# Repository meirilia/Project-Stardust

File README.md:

# Project Stardust

A custom keyboard created to mimick the layout of thinkpad's keyboard + some layout improvement (i guess).

**The layout :**

PCB for trackpoint module will come soon (hopefully...) + The application for directly configuring the keyboard

I will not procrastinate 
I will not procrastinate 
I will not procrastinate 
I will not procrastinate 
I will not procrastinate 
I will not procrastinate

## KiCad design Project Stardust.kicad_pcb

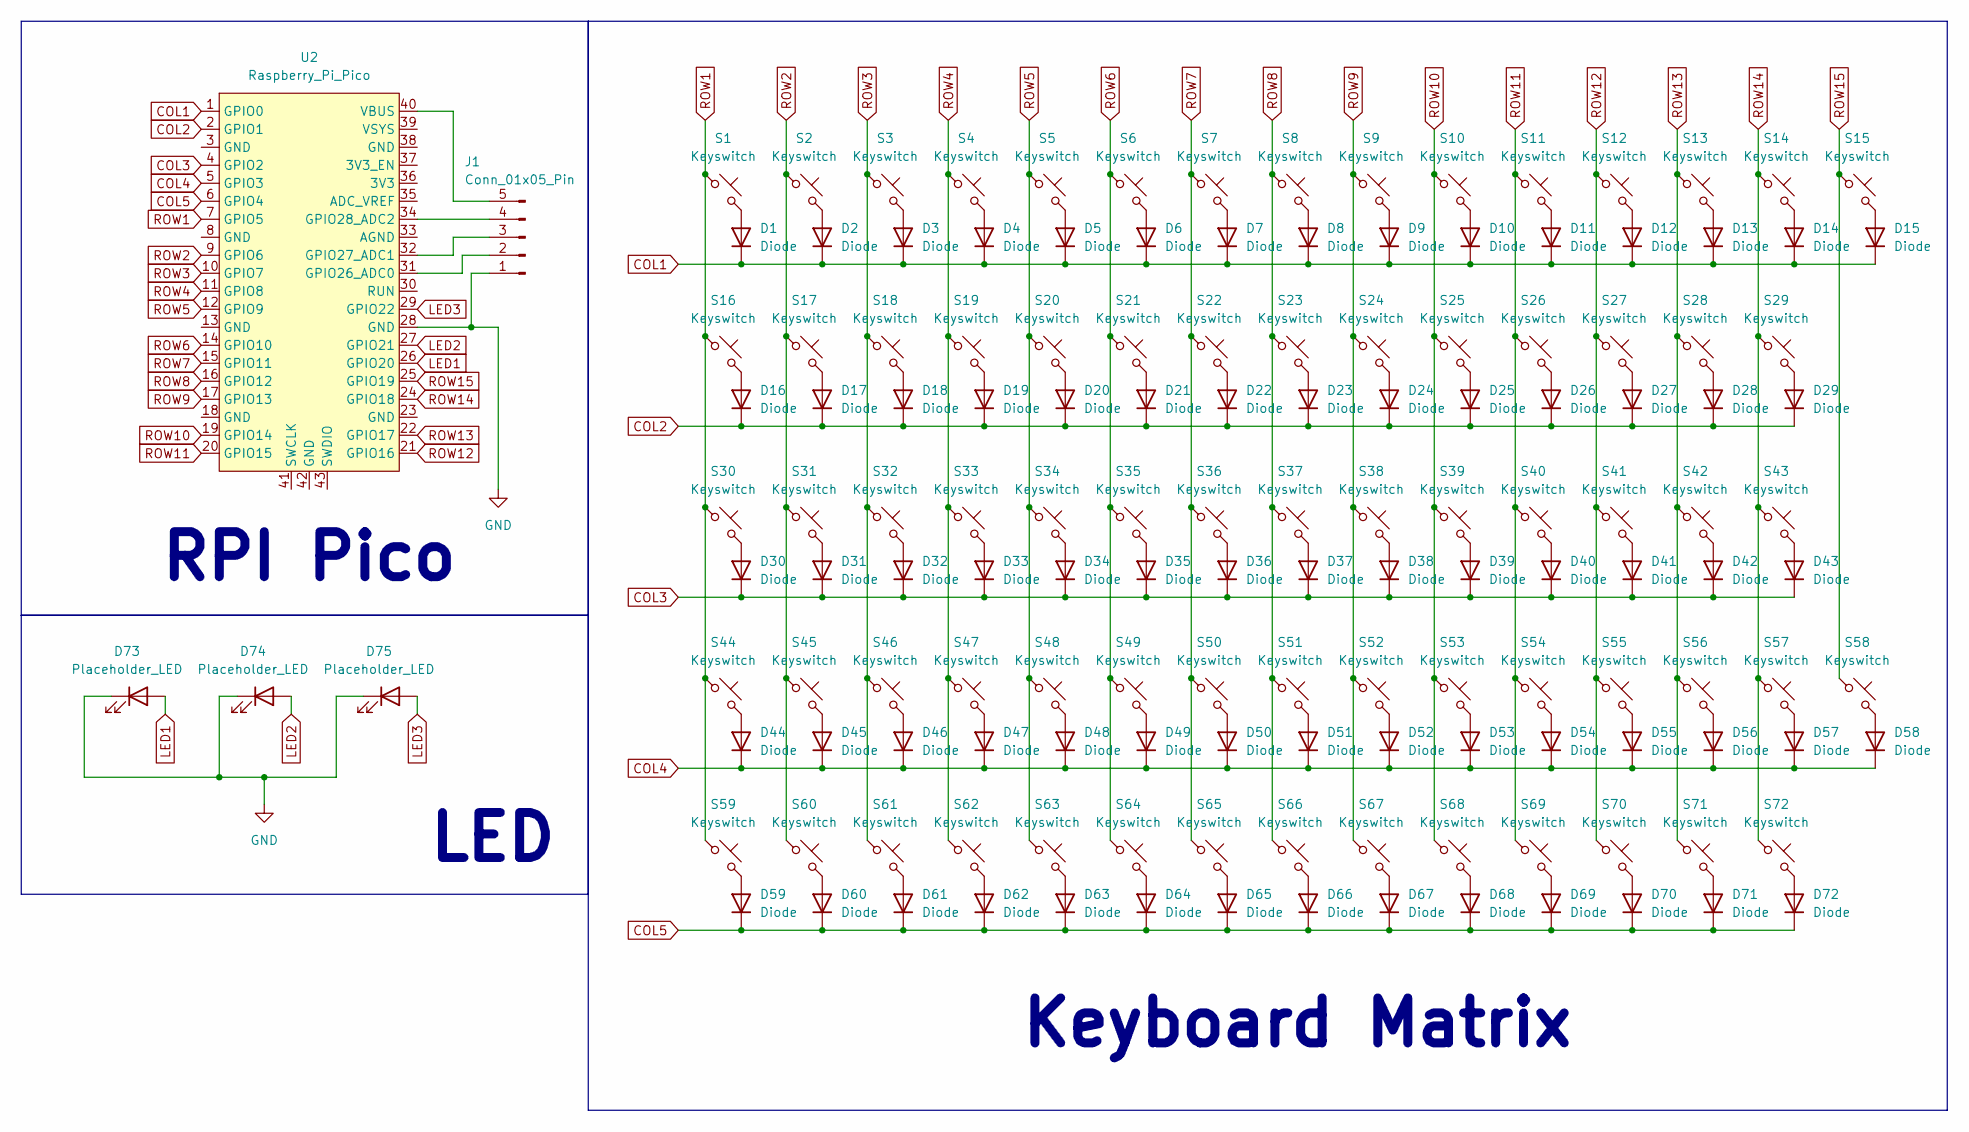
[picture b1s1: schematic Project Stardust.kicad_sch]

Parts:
D1, D2, D3, D4, D5, D6, D7, D8, D9, D10, D11, D12, D13, D14, D15, D16, D17, D18, D19, D20, D21, D22, D23, D24, D25, D26, D27, D28, D29, D30, D31, D32, D33, D34, D35, D36, D37, D38, D39, D40, D41, D42, D43, D44, D45, D46, D47, D48, D49, D50, D51, D52, D53, D54, D55, D56, D57, D58, D59, D60, D61, D62, D63, D64, D65, D66, D67, D68, D69, D70, D71, D72: Diode; Diode_DO-35
D73, D74, D75: Placeholder_LED; LED_D5.0mm
J1: Conn_01x05_Pin; SolderWire-0.5sqmm_1x05_P4.8mm_D0.9mm_OD2.3mm_Relief
S1, S2, S3, S4, S5, S6, S7, S8, S9, S10, S11, S12, S13, S14, S15, S17, S18, S19, S20, S21, S22, S23, S24, S25, S26, S27, S28, S31, S32, S33, S34, S35, S36, S37, S38, S39, S40, S41, S43, S45, S46, S47, S48, S49, S50, S51, S52, S53, S55, S56, S57, S58, S59, S61, S62, S64, S65, S66, S69, S70, S71, S72: Keyswitch; Hotswap_MX_1.00u
S16, S29: Keyswitch; Hotswap_MX_1.50u
S30, S54: Keyswitch; Hotswap_MX_1.75u
S42, S44, S63: Keyswitch; Hotswap_MX_2.25u
S60, S68: Keyswitch; Hotswap_MX_1.25u
S67: Keyswitch; Hotswap_MX_2.75u
U2: Raspberry_Pi_Pico

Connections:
COL1: D1.1 (K), D2.1 (K), D3.1 (K), D4.1 (K), D5.1 (K), D6.1 (K), D7.1 (K), D8.1 (K), D9.1 (K), D10.1 (K), D11.1 (K), D12.1 (K), D13.1 (K), D14.1 (K), D15.1 (K), U2.1 (GPIO0)
COL2: D16.1 (K), D17.1 (K), D18.1 (K), D19.1 (K), D20.1 (K), D21.1 (K), D22.1 (K), D23.1 (K), D24.1 (K), D25.1 (K), D26.1 (K), D27.1 (K), D28.1 (K), D29.1 (K), U2.2 (GPIO1)
COL3: D30.1 (K), D31.1 (K), D32.1 (K), D33.1 (K), D34.1 (K), D35.1 (K), D36.1 (K), D37.1 (K), D38.1 (K), D39.1 (K), D40.1 (K), D41.1 (K), D42.1 (K), D43.1 (K), U2.4 (GPIO2)
COL4: D44.1 (K), D45.1 (K), D46.1 (K), D47.1 (K), D48.1 (K), D49.1 (K), D50.1 (K), D51.1 (K), D52.1 (K), D53.1 (K), D54.1 (K), D55.1 (K), D56.1 (K), D57.1 (K), D58.1 (K), U2.5 (GPIO3)
COL5: D59.1 (K), D60.1 (K), D61.1 (K), D62.1 (K), D63.1 (K), D64.1 (K), D65.1 (K), D66.1 (K), D67.1 (K), D68.1 (K), D69.1 (K), D70.1 (K), D71.1 (K), D72.1 (K), U2.6 (GPIO4)
GND: D73.1 (K), D74.1 (K), D75.1 (K), J1.1, U2.28 (GND)
LED1: D73.2 (A), U2.26 (GPIO20)
LED2: D74.2 (A), U2.27 (GPIO21)
LED3: D75.2 (A), U2.29 (GPIO22)
unnamed: D1.2 (A), S1.2
unnamed: D2.2 (A), S2.2
unnamed: D3.2 (A), S3.2
unnamed: D4.2 (A), S4.2
unnamed: D5.2 (A), S5.2
unnamed: D6.2 (A), S6.2
unnamed: D7.2 (A), S7.2
unnamed: D8.2 (A), S8.2
unnamed: D9.2 (A), S9.2
unnamed: D10.2 (A), S10.2
unnamed: D11.2 (A), S11.2
unnamed: D12.2 (A), S12.2
unnamed: D13.2 (A), S13.2
unnamed: D14.2 (A), S14.2
unnamed: D15.2 (A), S15.2
unnamed: D16.2 (A), S16.2
unnamed: D17.2 (A), S17.2
unnamed: D18.2 (A), S18.2
unnamed: D19.2 (A), S19.2
unnamed: D20.2 (A), S20.2
unnamed: D21.2 (A), S21.2
unnamed: D22.2 (A), S22.2
unnamed: D23.2 (A), S23.2
unnamed: D24.2 (A), S24.2
unnamed: D25.2 (A), S25.2
unnamed: D26.2 (A), S26.2
unnamed: D27.2 (A), S27.2
unnamed: D28.2 (A), S28.2
unnamed: D29.2 (A), S29.2
unnamed: D30.2 (A), S30.2
unnamed: D31.2 (A), S31.2
unnamed: D32.2 (A), S32.2
unnamed: D33.2 (A), S33.2
unnamed: D34.2 (A), S34.2
unnamed: D35.2 (A), S35.2
unnamed: D36.2 (A), S36.2
unnamed: D37.2 (A), S37.2
unnamed: D38.2 (A), S38.2
unnamed: D39.2 (A), S39.2
unnamed: D40.2 (A), S40.2
unnamed: D41.2 (A), S41.2
unnamed: D42.2 (A), S42.2
unnamed: D43.2 (A), S43.2
unnamed: D44.2 (A), S44.2
unnamed: D45.2 (A), S45.2
unnamed: D46.2 (A), S46.2
unnamed: D47.2 (A), S47.2
unnamed: D48.2 (A), S48.2
unnamed: D49.2 (A), S49.2
unnamed: D50.2 (A), S50.2
unnamed: D51.2 (A), S51.2
unnamed: D52.2 (A), S52.2
unnamed: D53.2 (A), S53.2
unnamed: D54.2 (A), S54.2
unnamed: D55.2 (A), S55.2
unnamed: D56.2 (A), S56.2
unnamed: D57.2 (A), S57.2
unnamed: D58.2 (A), S58.2
unnamed: D59.2 (A), S59.2
unnamed: D60.2 (A), S60.2
unnamed: D61.2 (A), S61.2
unnamed: D62.2 (A), S62.2
unnamed: D63.2 (A), S63.2
unnamed: D64.2 (A), S64.2
unnamed: D65.2 (A), S65.2
unnamed: D66.2 (A), S66.2
unnamed: D67.2 (A), S67.2
unnamed: D68.2 (A), S68.2
unnamed: D69.2 (A), S69.2
unnamed: D70.2 (A), S70.2
unnamed: D71.2 (A), S71.2
unnamed: D72.2 (A), S72.2
unnamed: J1.2, U2.31 (GPIO26_ADC0)
unnamed: J1.3, U2.32 (GPIO27_ADC1)
unnamed: J1.4, U2.34 (GPIO28_ADC2)
unnamed: J1.5, U2.40 (VBUS)
ROW1: S1.1, S16.1, S30.1, S44.1, S59.1, U2.7 (GPIO5)
ROW2: S2.1, S17.1, S31.1, S45.1, S60.1, U2.9 (GPIO6)
ROW3: S3.1, S18.1, S32.1, S46.1, S61.1, U2.10 (GPIO7)
ROW4: S4.1, S19.1, S33.1, S47.1, S62.1, U2.11 (GPIO8)
ROW5: S5.1, S20.1, S34.1, S48.1, S63.1, U2.12 (GPIO9)
ROW6: S6.1, S21.1, S35.1, S49.1, S64.1, U2.14 (GPIO10)
ROW7: S7.1, S22.1, S36.1, S50.1, S65.1, U2.15 (GPIO11)
ROW8: S8.1, S23.1, S37.1, S51.1, S66.1, U2.16 (GPIO12)
ROW9: S9.1, S24.1, S38.1, S52.1, S67.1, U2.17 (GPIO13)
ROW10: S10.1, S25.1, S39.1, S53.1, S68.1, U2.19 (GPIO14)
ROW11: S11.1, S26.1, S40.1, S54.1, S69.1, U2.20 (GPIO15)
ROW12: S12.1, S27.1, S41.1, S55.1, S70.1, U2.21 (GPIO16)
ROW13: S13.1, S28.1, S42.1, S56.1, S71.1, U2.22 (GPIO17)
ROW14: S14.1, S29.1, S43.1, S57.1, S72.1, U2.24 (GPIO18)
ROW15: S15.1, S58.1, U2.25 (GPIO19)

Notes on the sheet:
LED
RPI Pico
Keyboard Matrix

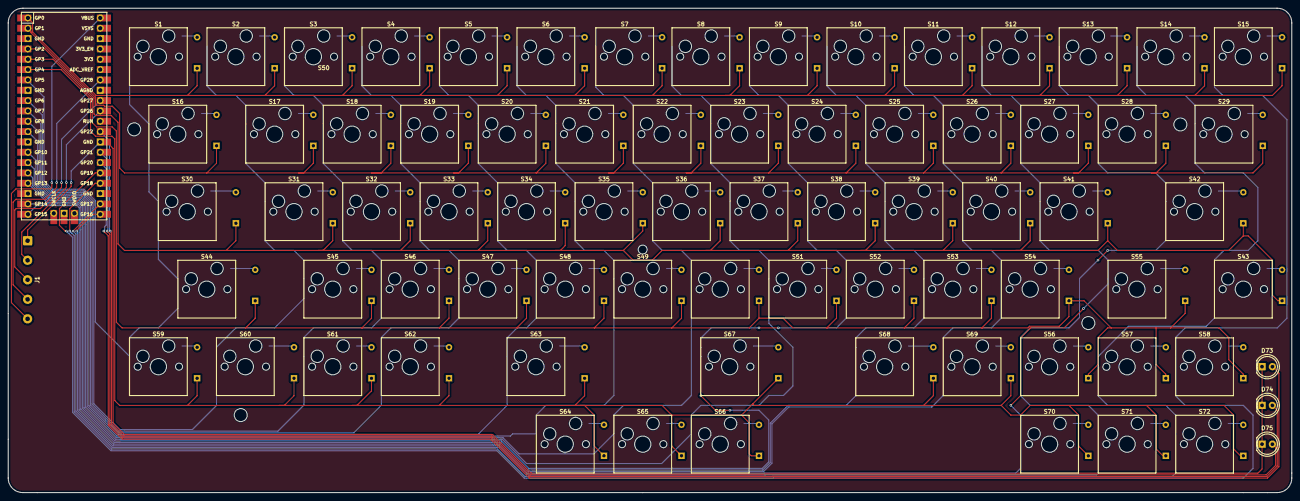
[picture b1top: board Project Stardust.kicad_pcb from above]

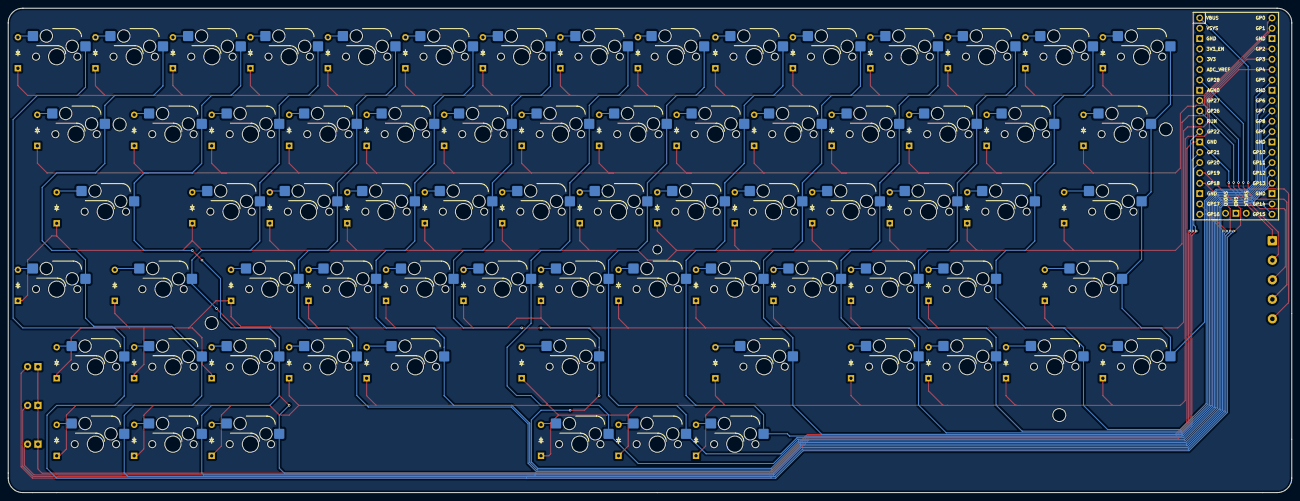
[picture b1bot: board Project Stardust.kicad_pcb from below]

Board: 2 copper layers, 315.5 x 119.1 mm, 149 parts (72 on the bottom side), 100 nets.

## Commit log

2023-07-16 readme
2025-01-12 New file!!!
